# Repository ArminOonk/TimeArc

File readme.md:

# Preparing the raspberry pi

## Update and install packages
Use the following commands to get the RPi ready

	sudo apt-get remove --purge desktop-base lightdm lxappearance lxde-common lxde-icon-theme lxinput lxpanel lxpolkit lxrandr lxsession-edit lxshortcut lxtask lxterminal
	sudo apt-get remove --purge obconf openbox raspberrypi-artwork 
	sudo apt-get remove --purge xarchiver xinit xserver-xorg 
	sudo apt-get remove --purge xserver-xorg-video-fbdev x11-utils x11-common x11-session utils
	sudo apt-get remove wolfram-*
	sudo apt-get update
	sudo apt-get upgrade
	sudo apt-get autoremove
	sudo rpi-update

# ESP Wifi
To get the esp wifi working first check the hardware. The APR2016 version has an error in the schematic. CH_PD is not connected to the correct pin.

In stall the driver using the instruction on the following website: http://oshlab.com/esp8266-raspberry-pi-gpio-wifi/

	cd ~
	git clone https://github.com/oshlab/esp8089.git
	cd esp8089
	sudo sh install
	sudo reboot
	sudo iwlist scan
	ifconfig

Check if wlan0 is visible. Now connect it to the wifi
	
	sudo nano /etc/wpa_supplicant/wpa_supplicant.conf

	network={
	ssid="testing"
	psk="testingPassword"
	}
	
Run the following commands if there is no internet connection (Test by using `ping 8.8.8.8`)

	sudo ifdown wlan0
	sudo ifup wlan0

# Install instructions

## Python packages
install pyfeed-0.7.4 and xe-0.7.4 from the Software directory

## Settings
Create a timearcPrivate.py file using the example

Add the following lines to /etc/rc.local

	sleep 30
	/home/pi/timearc/Software/startup

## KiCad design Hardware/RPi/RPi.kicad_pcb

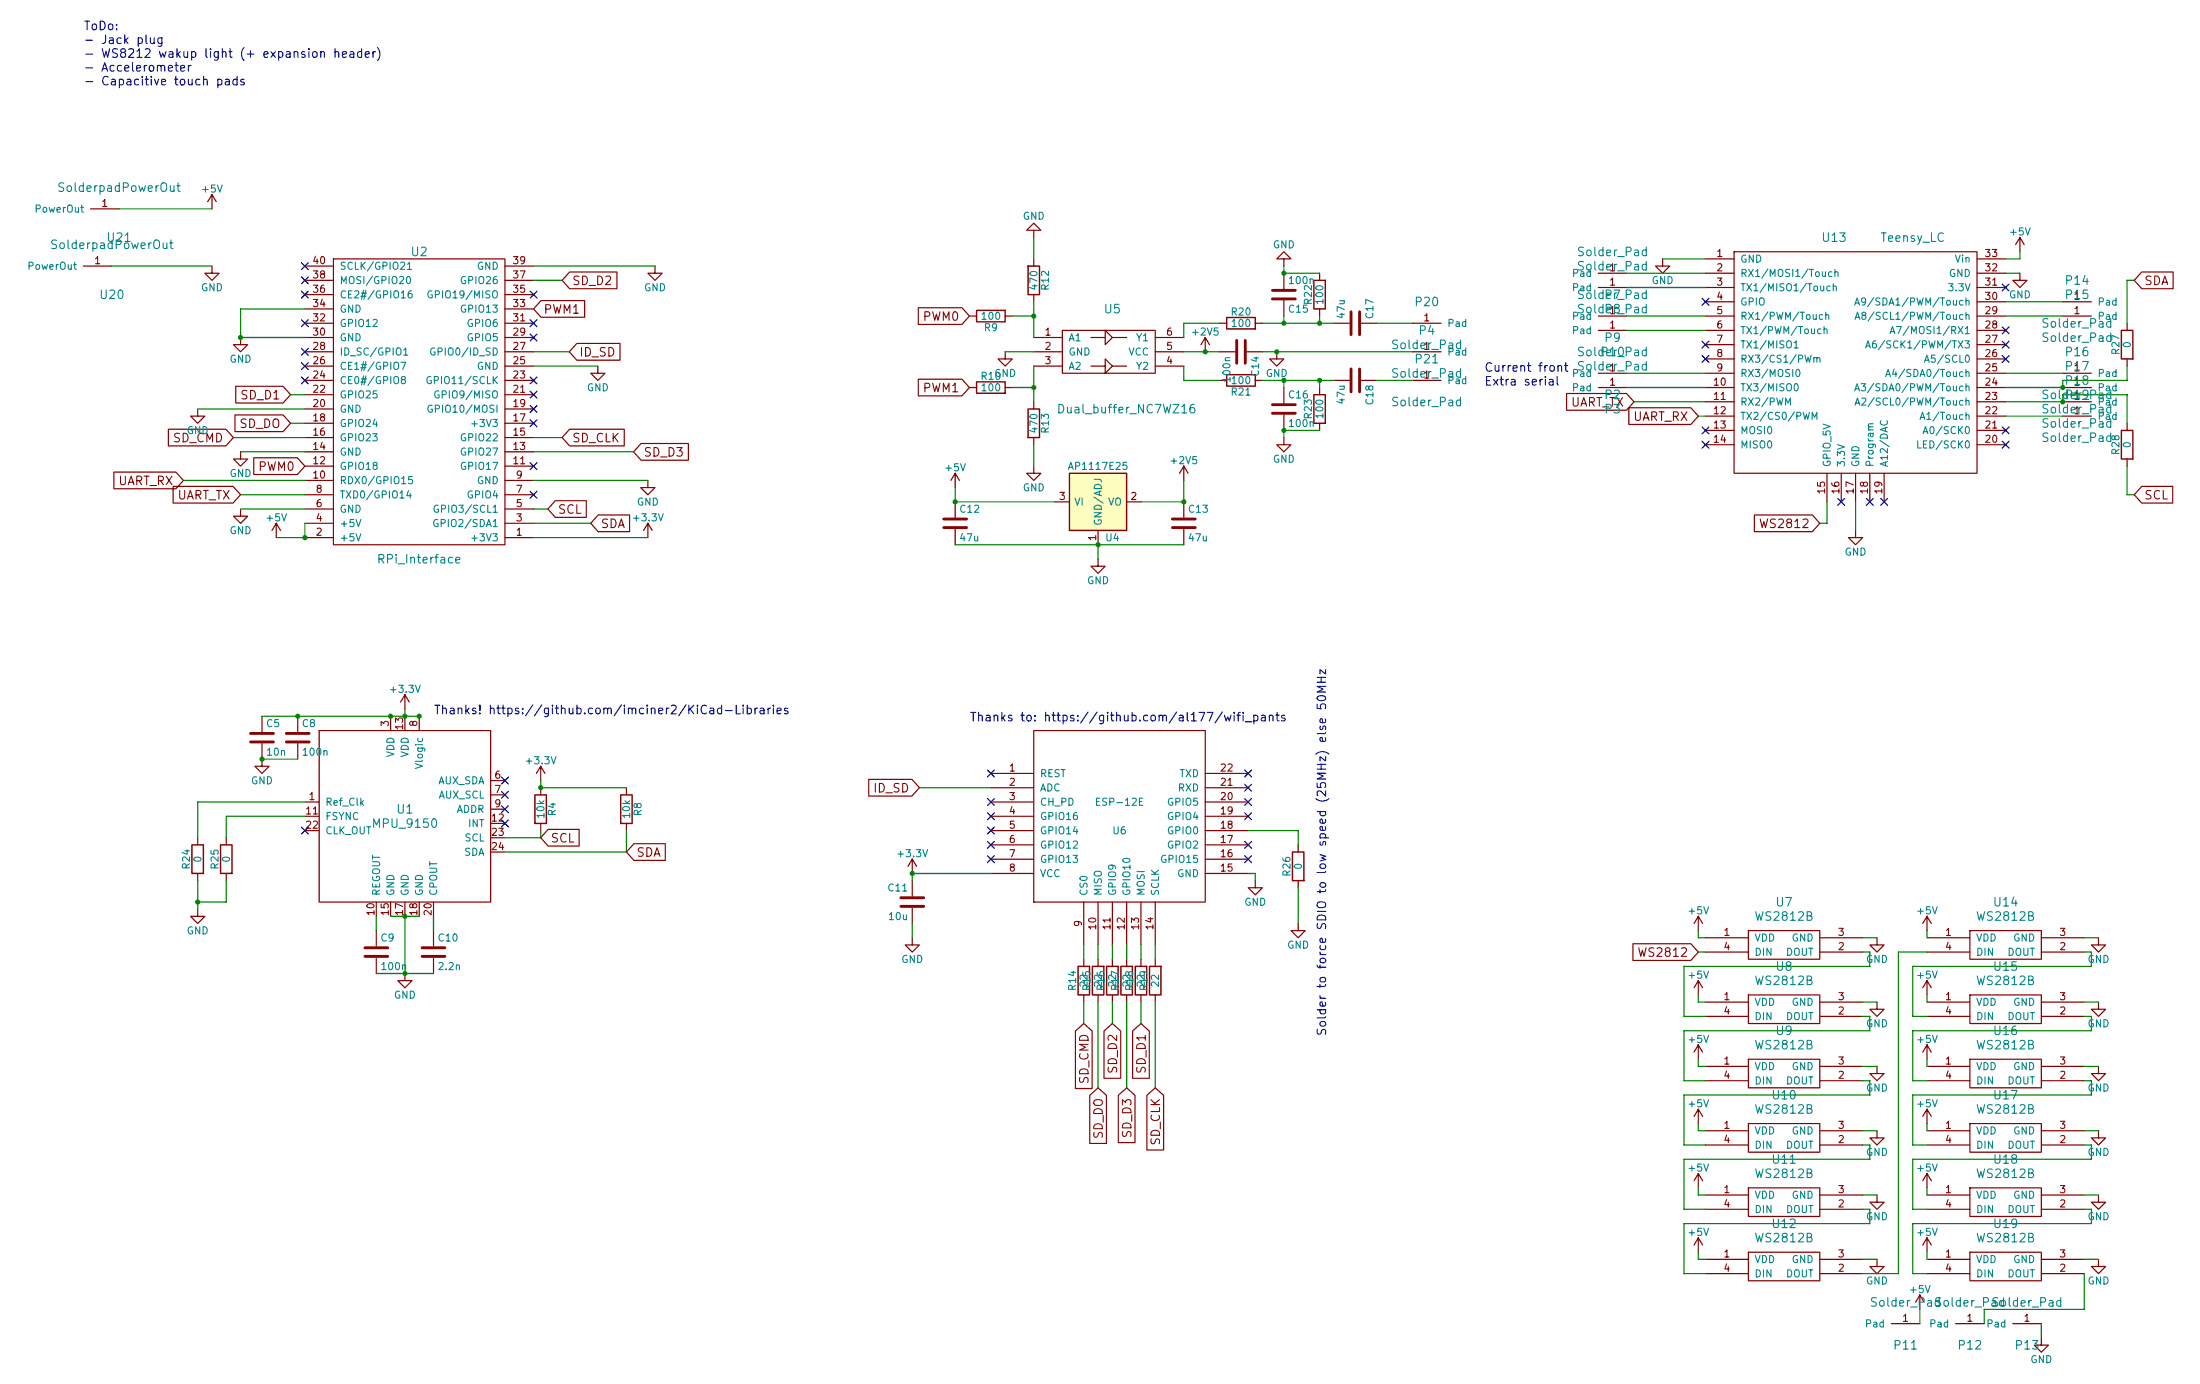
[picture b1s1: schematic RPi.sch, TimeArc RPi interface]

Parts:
C5: 10n; C_0603
C8, C9, C14, C15, C16: 100n; C_0603
C10: 2.2n; C_0603
C11: 10u; C_0603
C12, C13, C17, C18: 47u; C_0805
P2, P3, P4, P7, P8, P9, P10, P11, P12, P13, P14, P15, P16, P17, P18, P19, P20, P21: Solder_Pad; Measurement_Point_Square-SMD-Pad_Big
R4, R8: 10k; R_0603
R9, R10, R20, R21, R22, R23: 100; R_0603
R12, R13: 470; R_0603
R14, R15, R16, R17, R18, R19: 22; R_0603
R24, R25, R26, R27, R28: 0; R_0603
U1: MPU_9150; IMU9150
U2: RPi_Interface; RPi_Zero_farnell_1256663
U4: AP1117E25; SOT-223
U5: Dual_buffer_NC7WZ16; SC-70-6_Handsoldering
U6: ESP-12E
U7, U8, U9, U10, U11, U12, U14, U15, U16, U17, U18, U19: WS2812B; PLCC4-5050
U13: Teensy_LC; TeensyLC
U20, U21: SolderpadPowerOut; Measurement_Point_Square-SMD-Pad_Big

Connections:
+2V5: C13.1, C14.2, U4.2 (VO), U5.5 (VCC)
+3V3: C5.1, C8.1, C11.1, R4.1, R8.1, U1.3 (VDD), U1.8 (Vlogic), U1.13 (VDD), U2.1 (+3V3), U6.8 (VCC)
+5V: C12.1, P11.1, U2.2 (+5V), U2.4 (+5V), U4.3 (VI), U7.1 (VDD), U8.1 (VDD), U9.1 (VDD), U10.1 (VDD), U11.1 (VDD), U12.1 (VDD), U13.33 (Vin), U14.1 (VDD), U15.1 (VDD), U16.1 (VDD), U17.1 (VDD), U18.1 (VDD), U19.1 (VDD), U21.1
GND: C5.2, C8.2, C9.2, C10.2, C11.2, C12.2, C13.2, C14.1, C15.2, C16.2, P4.1, P13.1, R12.2, R13.2, R22.2, R23.2, R24.2, R25.2, R26.2, U1.15 (GND), U1.17 (GND), U1.18 (GND), U2.6 (GND), U2.9 (GND), U2.14 (GND), U2.20 (GND), U2.25 (GND), U2.30 (GND), U2.34 (GND), U2.39 (GND), U4.1 (GND/ADJ), U5.2 (GND), U6.15 (GND), U7.3 (GND), U8.3 (GND), U9.3 (GND), U10.3 (GND), U11.3 (GND), U12.3 (GND), U13.1 (GND), U13.17 (GND), U13.32 (GND), U14.3 (GND), U15.3 (GND), U16.3 (GND), U17.3 (GND), U18.3 (GND), U19.3 (GND), U20.1
ID_SD: U2.27 (GPIO0/ID_SD), U6.2 (ADC)
unnamed: C9.1, U1.10 (REGOUT)
unnamed: C10.1, U1.20 (CPOUT)
unnamed: C15.1, C17.2, R20.2, R22.1
unnamed: C16.1, C18.2, R21.2, R23.1
unnamed: C17.1, P20.1
unnamed: C18.1, P21.1
unnamed: P2.1, U13.9 (RX3/MOSI0)
unnamed: P3.1, U13.10 (TX3/MISO0)
unnamed: P7.1, U13.2 (RX1/MOSI1/Touch)
unnamed: P8.1, U13.3 (TX1/MISO1/Touch)
unnamed: P9.1, U13.5 (RX1/PWM/Touch)
unnamed: P10.1, U13.6 (TX1/PWM/Touch)
unnamed: P12.1, U19.2 (DOUT)
unnamed: P14.1, U13.30 (A9/SDA1/PWM/Touch)
unnamed: P15.1, U13.29 (A8/SCL1/PWM/Touch)
unnamed: P16.1, U13.25 (A4/SDA0/Touch)
unnamed: P17.1, R27.2, U13.24 (A3/SDA0/PWM/Touch)
unnamed: P18.1, R28.1, U13.23 (A2/SCL0/PWM/Touch)
unnamed: P19.1, U13.22 (A1/Touch)
unnamed: R10.2, R13.1, U5.3 (A2)
unnamed: R9.2, R12.1, U5.1 (A1)
unnamed: R14.2, U6.9 (CS0)
unnamed: R15.2, U6.10 (MISO)
unnamed: R16.2, U6.11 (GPIO9)
unnamed: R17.2, U6.12 (GPIO10)
unnamed: R18.2, U6.13 (MOSI)
unnamed: R19.2, U6.14 (SCLK)
unnamed: R20.1, U5.6 (Y1)
unnamed: R21.1, U5.4 (Y2)
unnamed: R24.1, U1.1 (Ref_Clk)
unnamed: R25.1, U1.11 (FSYNC)
unnamed: R26.1, U6.18 (GPIO0)
unnamed: U7.2 (DOUT), U8.4 (DIN)
unnamed: U8.2 (DOUT), U9.4 (DIN)
unnamed: U10.2 (DOUT), U11.4 (DIN)
unnamed: U9.2 (DOUT), U10.4 (DIN)
unnamed: U11.2 (DOUT), U12.4 (DIN)
unnamed: U12.2 (DOUT), U14.4 (DIN)
unnamed: U14.2 (DOUT), U15.4 (DIN)
unnamed: U15.2 (DOUT), U16.4 (DIN)
unnamed: U16.2 (DOUT), U17.4 (DIN)
unnamed: U17.2 (DOUT), U18.4 (DIN)
unnamed: U18.2 (DOUT), U19.4 (DIN)
PWM0: R9.1, U2.12 (GPIO18)
PWM1: R10.1, U2.33 (GPIO13)
SCL: R4.2, R28.2, U1.23 (SCL), U2.5 (GPIO3/SCL1)
SDA: R8.2, R27.1, U1.24 (SDA), U2.3 (GPIO2/SDA1)
SD_CLK: R19.1, U2.15 (GPIO22)
SD_CMD: R14.1, U2.16 (GPIO23)
SD_D1: R18.1, U2.22 (GPIO25)
SD_D2: R16.1, U2.37 (GPIO26)
SD_D3: R17.1, U2.13 (GPIO27)
SD_DO: R15.1, U2.18 (GPIO24)
UART_RX: U2.10 (RDX0/GPIO15), U13.12 (TX2/CS0/PWM)
UART_TX: U2.8 (TXD0/GPIO14), U13.11 (RX2/PWM)
WS2812: U7.4 (DIN), U13.15 (GPIO_5V)

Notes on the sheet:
Solder to force SDIO to low speed (25MHz) else 50MHz
Thanks to: https://github.com/al177/wifi_pants
ToDo: - Jack plug - WS8212 wakup light (+ expansion header) - Accelerometer - Capacitive touch pads
Thanks! https://github.com/imciner2/KiCad-Libraries
Current front Extra serial

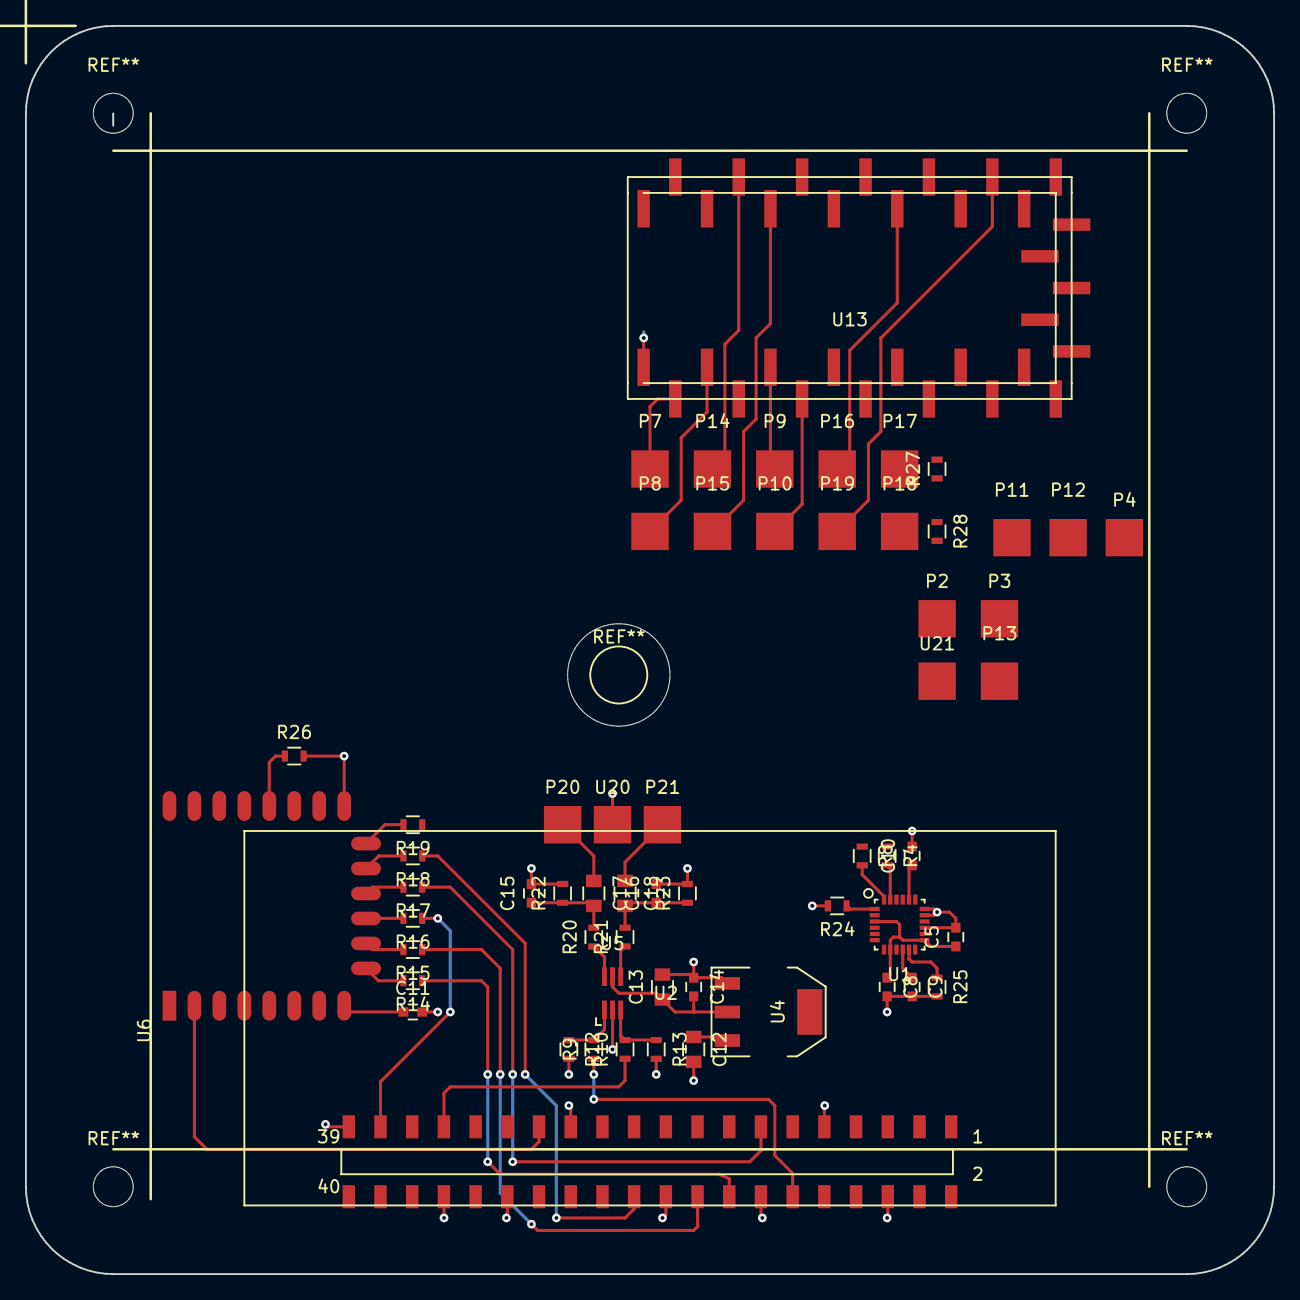
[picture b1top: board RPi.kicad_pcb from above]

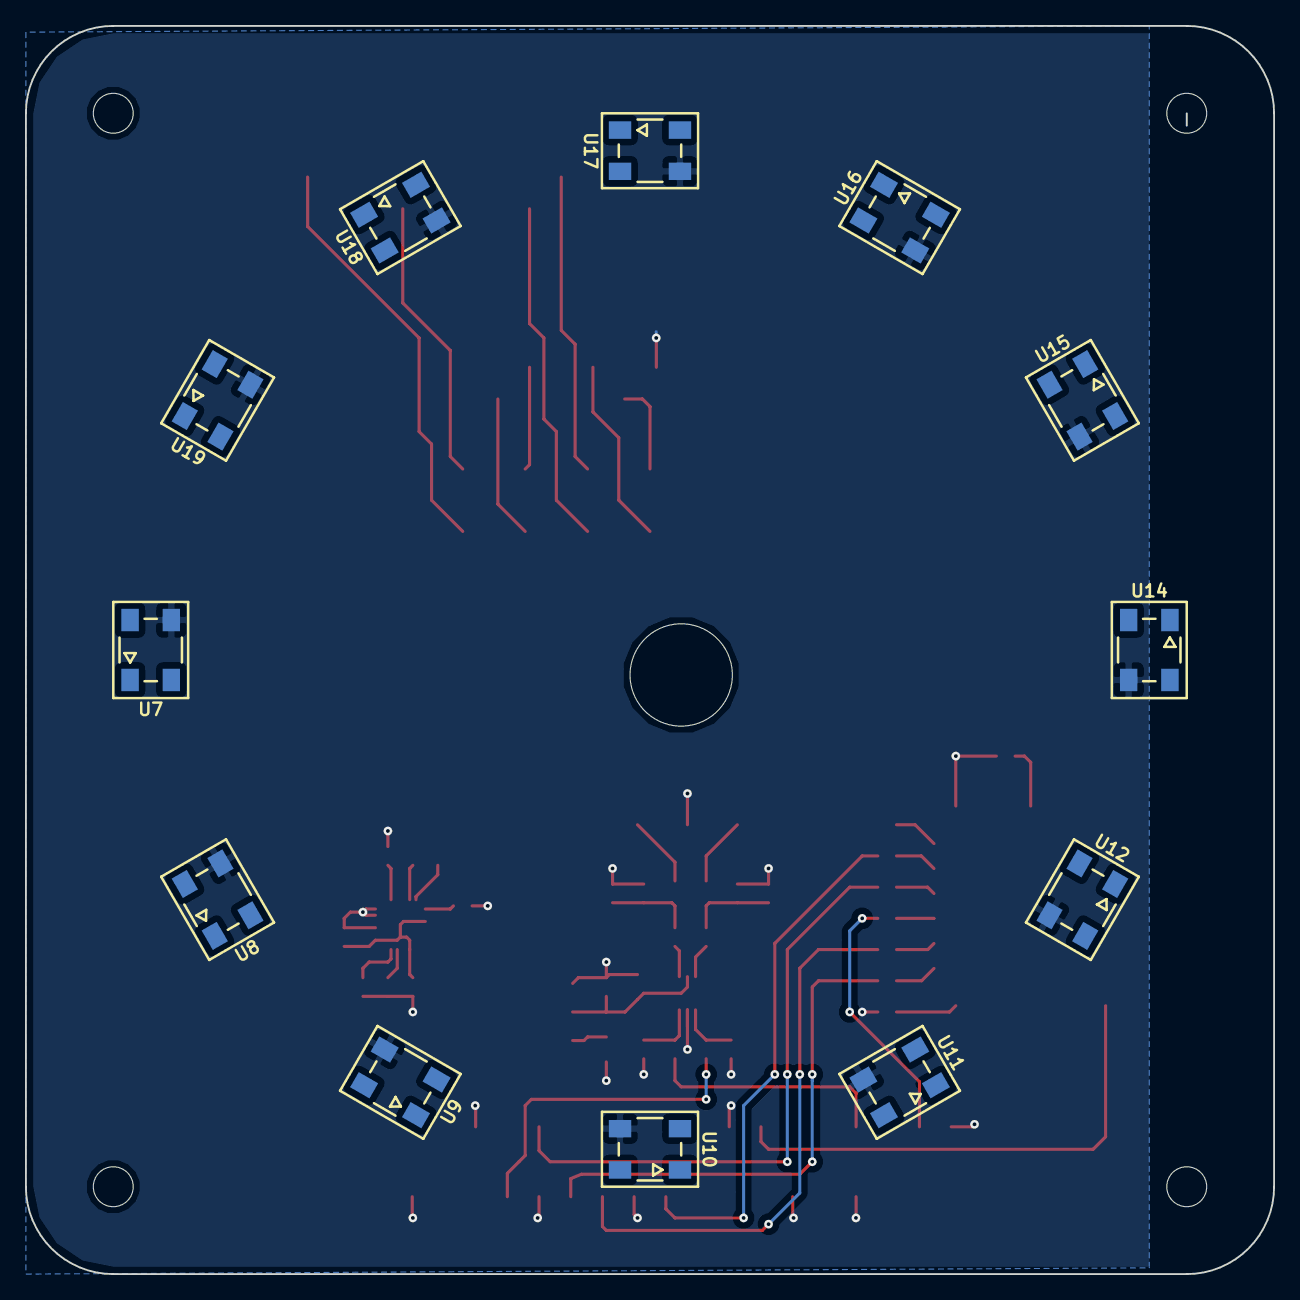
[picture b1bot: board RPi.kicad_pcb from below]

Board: 2 copper layers, 100.0 x 100.0 mm, 71 parts (12 on the bottom side), 61 nets.

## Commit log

2014-04-12 Arcdozen 2 toegevoegd
2014-04-13 Arcdozen arc
2014-04-13 arcdozen2
2014-04-13 Leds aangesloten
2014-04-13 New via
2014-04-13 Outer Vias
2014-04-13 arcdozen arcs
2014-04-13 arcdozen traces
2014-04-13 more traces
2014-04-13 traces leds complete (for now)
2014-04-14 Connected traces
2014-04-14 Hour traces
2014-04-14 4 layer
2014-04-14 64 pin Micro geplaatst
2014-04-14 condensatoren
2014-04-14 32KHz crystal
2014-04-15 Changed micro to stm32f103 144pins
2014-04-15 connecting some leds
2014-04-15 Moved silk to tdocu and rearranged arcdozen
2014-04-15 routing
2014-04-16 Placing components, change to custom components
2014-04-16 Start power subsystem
2014-04-16 Drill size via's naar 0.31
2014-04-19 Trying to get a 100x100mm board for ditypcb.com
2014-04-19 Layout power system
2014-04-19 Modified schematic, added adxl345
2014-04-19 Added accelerometer datasheet ADXL345
2014-04-19 Connected the accelerometer adxl345
2014-04-19 Wake Up Leds 5mm
2014-04-19 placed wake up light
2014-04-19 traces
2014-04-20 Added cc3000 wifi
2014-04-20 cc3300 on board
2014-04-21 ti capacitive touch design
2014-04-21 Light sensor added, wifi connected to spi2
2014-04-21 Debug serial port
2014-04-21 usb added
2014-04-21 placed USB
2014-04-21 starting sound system
2014-04-23 Audio amp added
2014-04-25 Removed parts
2014-04-25 Moved to 2 layer
2014-04-25 64 pin microcontroller
2014-04-25 connecting
2014-04-25 connect led matrix
2014-04-25 all within dimension lines
2014-04-26 Board outline and mounting
2014-04-26 routing, rotated design 180
2014-04-29 Touch pad
2014-04-29 touch pad place
2014-04-29 touch connected
2014-04-29 last touch
2014-04-30 connected wake
2014-04-30 placing specials
2014-04-30 placing special
2014-04-30 special connecten almost done
2014-05-05 final trace?
2014-05-05 added 3v3 to program header
2014-05-05 silkscreen
2014-05-06 center top button
2014-05-06 design rules dirty cheap boards
2014-05-06 added numerals
2014-05-06 cleanup schematic
2014-05-06 starting BOM
2014-05-06 BOM finished
2014-05-07 mirrored output CAM
2014-05-07 added production gerbers
2014-05-07 added spacer to BOM
2014-05-08 Added board outline to gerber
2014-05-27 Updated order code
2014-05-27 Moved everything to hardware folder
2014-05-27 Initial commit firmware
2014-05-27 Hardware pin definitions
2014-05-28 Demo code
2014-05-28 Interrupt driven demo, all leds on
2014-05-28 Starting displayBuffer
2014-05-28 Added hour/minute/second functions
2014-05-28 Demo Clock
2014-05-29 Added a display buffer
2014-05-29 Touch2 test code interrupt driven
2014-05-29 capTouch class
2014-05-29 Added second touch button, new demo
2014-05-29 4 touch buttons added incl demo
2014-05-29 Added intensity setting to display
2014-06-02 Hardware fix: hack wire connecting touchdown to PC13 Software fix: demo touch
2014-06-02 Reading accelero data
2014-06-02 interrupts accel
2014-06-03 working accel
2014-06-03 Moved accelerometer to its own class
2014-06-03 interrupt accel keeps firing
2014-06-04 Added pose calculation based on accel DATA refactored display buffer to prepare it for pose data
2014-06-04 Tweaked the pose parameters
2014-06-04 demo pose and different display modes
2014-06-04 Trying LSE
2014-06-05 Working serial code
2014-06-05 Added pose and button serial feedback
2014-06-05 Trying adxl345 interupt -> bad solder contact
2014-06-06 working RTC code
2014-06-09 cleanup
2014-06-09 Creating rtc class
2014-06-09 Moved RTC code to its own class
2014-06-09 Added get/setting time from serial
2014-06-09 Added timezones
2014-06-09 Added daylight saving
2014-06-10 lightSensor in its own class
2014-06-10 Changed timezone&daylightsaving to generic offset print ID print MODE
2014-06-10 display setIntensity compensation added
2014-06-10 Added an auto mode
2014-06-12 ADXL345: read (polling) INT1, report tap detected
2014-06-12 layer drills off
2014-06-12 Auto off, wake up by tap or button
2014-06-12 Created keep out layer for lasercut
2014-06-12 Lasercut design files
2014-06-19 Lasercut files as ordered on snijlab.nl
2014-06-23 Fade in leds, when time is unknown set it to 0
2014-06-23 First software to control the TimeArc
2014-06-23 First test
2014-06-24 nothing important
2014-06-25 simple clock testing
2014-06-25 Moving serial code to its own class
2014-06-25 Moved serial code to its own class
2014-07-03 Added Linux support
2014-07-03 Going to python3
2014-07-03 chmod +x
2014-07-03 delay between time and offset
2014-07-03 Waiting for correct time
2014-07-03 Added timeout command
2014-07-03 Added print in timeout
2014-07-03 Added some sleep time
2014-07-03 Added some extra timeout calls because it does not work
2014-07-03 Added AUTO mode
2014-12-29 Fixed daylight saving time bug
2014-12-30 Added mpd demo, thread demo
2014-12-30 Moved threading alarm to its own class
2015-01-01 Put MPC control code in its own class
2015-01-01 Updated alarms, inputting hour,minute to trigger alarm
2015-01-01 Callback with sound
2015-01-04 pretty print time remaining
2015-01-04 Run communication check in seperate thread
2015-01-04 Button, accelero event callbacks
2015-01-04 Volume control
2015-01-04 Double tap is pause
2015-01-04 Improved pause function, also needs a TOP button event the last 2 seconds
2015-04-01 Google calendar example
2015-04-01 Added searching to query
2015-04-01 Prepared timearc for updating time
2015-04-02 Created an timearc GoogleCalendar class
2015-04-02 Example private file, used for google credentials
2015-04-04 Added an ignore file
2015-04-04 Google calendat integration. Completed?
2015-04-04 Some more tweaks
2015-05-04 Readme added
2015-05-04 Fixed typ
2015-05-04 Updated libraries
2015-05-04 Added a working mpd config
2015-05-04 Added modified gflags
2015-05-05 Removed state file from mpd.conf
2015-05-05 Decorator on MPD to check the connection
2015-05-05 Clean up
2015-05-05 Disabled decorator --> does not work yet. Using keep alive
2015-05-05 Changed audio pause into FRONT pose, seems to work better than double tap
2015-05-06 Added startup script called from /etc/rc.local
2015-05-06 Fixed ols python2 exceptions
2015-05-06 Typo
2015-05-09 Switching to logging functionality
2015-05-09 Moving to logging functionality
2015-05-09 Removing old logging utility
2015-05-09 Made the modules different in the logging output
2015-05-11 Setup log file
2015-05-18 Using timestamp to set alarm time, fix double alarm callback?
2015-05-18 Moved google calendar into alarm class
2015-11-15 Updated streams
2015-12-12 Adding webapplication
2015-12-12 Removed project file
2015-12-20 Changed timezone handeling
2015-12-23 Fixed pinguin radio links
2015-12-23 Enclosure sketch
2015-12-24 Subtracted bolt holes from 3d print part
2015-12-27 Improved standoff (keeps clear of programming port)
2015-12-28 USB hub added
2016-01-21 Side pcb with capacitive slider and enclosure
2016-02-10 Tweaked the board File.php Enclosure.skp jorrit ideas
2016-02-16 Raspbarry Pi zero mounting PCB
2016-02-16 Added USB hub
2016-02-18 Added Teensy LC, Wake up light WS2812
2016-02-22 Schematic RPi
2016-03-01 Creating footprints
2016-04-01 New hardware ideas
2016-04-04 netlist update
2016-04-05 Fixed schematic/component errors
2016-04-05 Led circular layout ULP
2016-04-06 Added libraries
2016-04-06 Trying to fix the teensyLC footprint
2016-04-06 Added gitignore
2016-04-06 Starting pcb layout
2016-04-07 Do not forget to run: sys.path.append('Script path')
    With forward slashes '/' NOT back slash '\\'
2016-04-10 Placing the leds almost circular
2016-04-11 Fixed first leds position wrong (Dirty hack)
2016-04-12 Removed FTDI header, removed all unused footprints
2016-04-13 Placing stuff on the board
2016-04-13 Removed USB hub, ordered pcb
2016-04-16 Restructure
2016-04-16 Starting back pcb in eagle
2016-04-19 Added Audio out
2016-04-19 Added Teensy LC SMD version
2016-04-21 Start routing board Back2016/back.brd Added keep out to Front2014/uac.brd Tweaked the 3d print design
2016-04-22 100% connected
2016-04-23 Tweaked the silk screen
2016-04-23 More small tweaks to the silkscreen
2016-04-25 Finished hardware design, added logo
2016-04-25 Increase logo resolution
2016-04-25 Added TimeArc Back APR2016 BOM
2016-04-25 Created an ulp to circular place on the BOTTOM (quick hack) Created schematic/board for a ws2811 driven front
2016-04-26 Connecting the seconds
2016-04-26 Connected rest of schematic, added solderpad for +5V, DIN, DOUT, GND Added a footprint for a capacitor in the ws8211 footprint
2016-04-27 100% routed, Updated the TIMEARC_KEEPOUT footprint to include the 4 drill holes
2016-04-27 Logo and silkscreen
2016-04-27 Gerbers and last tweaks to the board
2016-04-27 Fixed missing stop mask in large touchpad Added artwork
2016-05-03 Created the corner supports
2016-07-11 Creating version APR2016 of the back pcb
2016-07-11 Fixed stupid error in schematic
2016-07-11 Updating the readme
2017-10-19 Adding simple serial receive communication protocol
